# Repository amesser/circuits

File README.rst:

MPP Solar Battery Charger
=========================

This project is about creating a Maximum Power Point
Solar Battery Charger made of analog components only. I
also tried to use commonly available parts and
renounce using highly integrated and specialized ICs.

The charger uses a DC-DC Converter in Buck topology to
optimize the operating point of the solar panel. The optimal
operating voltage is manually adjustable. The charger will 
not dynamically adapt this voltage. (This would require
a microcontroller)

The circuit is made for 200W solar input power from 
36 cell panels and 12V Lead-Acid Battery. It can be 
easily adapted for other input and battery voltages.

More information can be found here: :doc:`documentation/index`

Licenses
--------

The following licensing conditions hold for this work:

Copyright (c) 2018 by Andreas Messer. This work is licensed under the 
Creative Commons Attribution-ShareAlike 3.0 Unported License. To view 
a copy of this license, visit http://creativecommons.org/licenses/by-sa/3.0/.

Author
------

Andreas Messer <andi@bastelmap.de>

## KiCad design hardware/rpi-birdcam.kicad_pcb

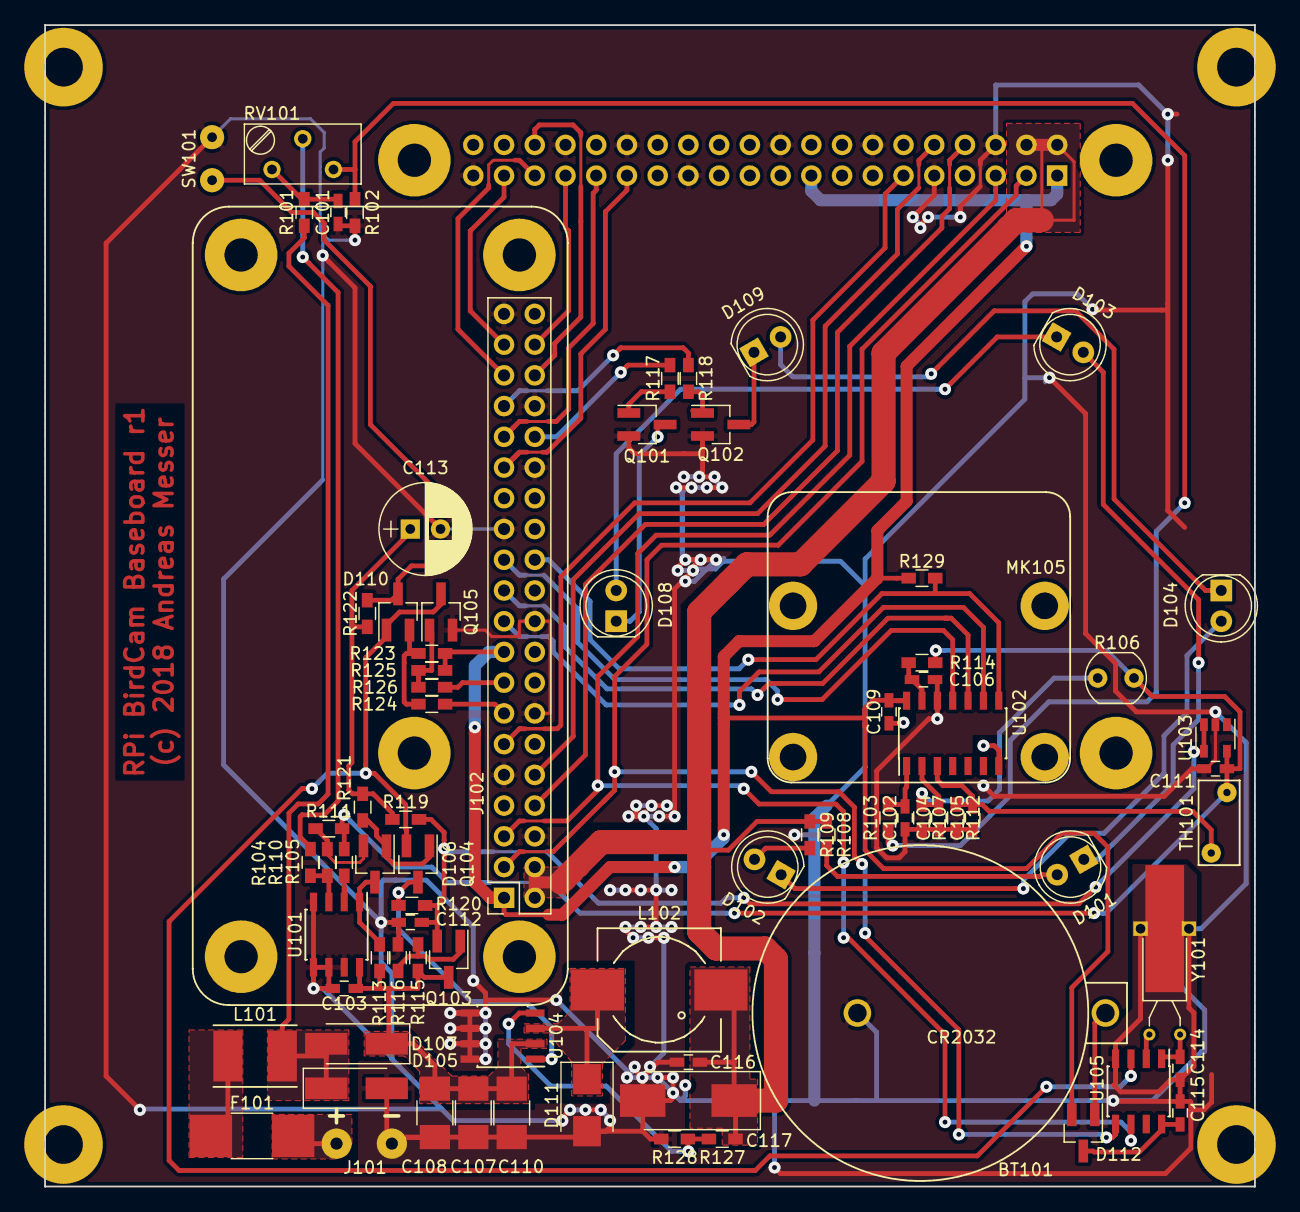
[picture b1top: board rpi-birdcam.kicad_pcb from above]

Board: 2 copper layers, 100.0 x 96.0 mm, 81 parts (1 on the bottom side), 63 nets.

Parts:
BT101: CR2032; keystone_electronics_106
C101, C102, C103, C104, C105, C106, C109, C111, C112, C116: 22nF; C_0603_HandSoldering
C107, C108, C110: 10µF; C_1210_HandSoldering
C113: 100µF; CP_Radial_D7.5mm_P2.50mm
C114: C; C_0603_HandSoldering
C115: 100nF; C_0603_HandSoldering
C117: 100µF; CP_Tantalum_Case-D_EIA-7343-31_Hand
D101, D102, D103, D104, D108, D109: LED; LED_D5.0mm
D105: D_TVS; D_SMA_Handsoldering
D106, D110, D112: BAT54C; SOT-23_Handsoldering
D107: SS14; D_SMA_Handsoldering
D111: SS22; D_SMB
F101: Polyfuse; R_1812_HandSoldering
J101: Conn_01x02; WireConnection_1.00mmDrill
J102: RPI; Raspberry_PI_Zero_V1.2_SocketStrip
J103: LTE Cat.1 Pi HAT; Raspberry_PI_ShieldConnector
L101: 47µH; Inductor_Taiyo-Yuden_NR-50xx_HandSoldering
L102: 22µH; Choke_SMD_Wuerth-WE-PDF_Handsoldering
MK103: Case; Kradex_Z59
MK105: Raspberry PI Camera Module V2.1; Raspberry_PI_Camera_Module_V2.1
Q101, Q102, Q103, Q104: BC847C; SOT-23_Handsoldering
Q105: Q_NPN_BEC; SOT-23_Handsoldering
R101: 22k; R_0603_HandSoldering
R102: 4.7k; R_0603_HandSoldering
R103, R104, R105, R107, R112: 100k; R_0603_HandSoldering
R106: LDR03; Resistor_LDR_5x4.1_RM3
R108, R109, R117, R118: R; R_0603_HandSoldering
R110, R113, R119: 470k; R_0603_HandSoldering
R111, R114, R122, R123, R125, R129: 10k; R_0603_HandSoldering
R115, R120: 47k; R_0603_HandSoldering
R116: 33k; R_0603_HandSoldering
R121: 2.2M; R_0603_HandSoldering
R124, R126: 1k; R_0603_HandSoldering
R127: 3.01k; R_0603_HandSoldering
R128: 976; R_0603_HandSoldering
RV101: 2k; Potentiometer_Trimmer_Bourns_3296Y
SW101: SW_Push; WireConnection_0.80mmDrill
TH101: PTC; RV_Disc_D7_W3.4_P5
U101: LM393; SOIC-8_3.9x4.9mm_Pitch1.27mm
U102: MCP3204; SOIC-14_3.9x8.7mm_Pitch1.27mm
U103: LM4120; SOT-23-5
U104: MIC4690; SOIC-8_3.9x4.9mm_Pitch1.27mm
U105: PCF8563; SOIC-8_3.9x4.9mm_Pitch1.27mm
Y101: 32.768 kHz; Crystal_AT310_d3.0mm_l10.0mm_Horizontal_1EP_style2

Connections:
/3.3V: C109.2, D112.2, J102.1, J102.17, J103.1, J103.17, R123.1, R125.1, R129.2, U102.14
/5V: C116.1, C117.1, J102.2, J102.4, J103.2, J103.4, L102.2, R108.1, R109.1, R127.2
/LTE_CTS: J102.36, J103.36
/LTE_DTR: J102.38, J103.33
/LTE_INH: J102.35, J103.35
/LTE_POWER: J102.29, J103.29
/LTE_RESET: J102.31, J103.31
/LTE_RST2: J102.37, J103.37
/LTE_RTS: J102.11, J103.11
/LTE_RXD: J102.10, J103.10
/LTE_TXD: J102.8, J103.8
/RPI_MISO: J102.21, U102.10
/RPI_MOSI: J102.19, U102.9
/RPI_SCL: J102.5, J103.5, U105.6
/RPI_SCLK: J102.23, U102.11
/RPI_SDA: J102.3, J103.3, U105.5
/VREF_2.5V: C111.1, R105.1, R106.1, R111.2, R114.2, TH101.1, U103.5
/~ADC_CE~: J102.24, R129.1, U102.8
/~PWR_BTN~: J102.13, R124.1
/~PWR_EN~: Q104.3, R120.2, U104.1
/~PWR_OFF~: J102.15, R126.1
/~PWR_ON~: D110.1, Q104.2, Q105.3, U105.3
/~UV~: D106.3, R113.2, U101.1
GND: BT101.2, C101.2, C102.1, C103.2, C104.1, C105.1, C106.2, C107.2, C108.2, C109.1, C110.2, C111.2, C112.2, C113.2, C114.2, C115.2, C116.2, C117.2, D105.2, D111.2, J101.2, J102.6, J102.9, J102.14, J102.20, J102.25, J102.30, J102.34, J102.39, J103.6, J103.9, J103.14, J103.20, J103.25, J103.30, J103.34, J103.39, Q101.2, Q102.2, Q105.2, R102.2, R107.2, R112.2, R116.2, R128.1, SW101.1, U101.4, U101.5, U101.6, U101.7, U102.7, U102.12, U103.2, U104.5, U104.6, U104.7, U104.8, U105.4, Y101.3
unnamed: BT101.1, D112.1
unnamed: C101.1, R101.2, RV101.1
unnamed: C102.2, R103.2, U102.1
unnamed: C103.1, C107.1, C108.1, C110.1, D107.1, Q103.3, R113.1, R115.1, U101.8, U104.2
unnamed: C104.2, R106.2, R107.1, U102.2
unnamed: C105.2, R112.1, TH101.2, U102.3
unnamed: C106.1, R114.1, U102.13
unnamed: C112.1, Q103.2, R119.2, R120.1, U103.3, U103.4
unnamed: C113.1, R119.1, R121.2, R122.2
unnamed: C114.1, U105.1, Y101.1
unnamed: C115.1, D112.3, U105.8
unnamed: D101.1, D103.2
unnamed: D101.2, R108.2
unnamed: D102.1, D104.2
unnamed: D102.2, R109.2
unnamed: D103.1, D108.2
unnamed: D104.1, D109.2
unnamed: D105.1, D107.2, L101.2, R101.1
unnamed: D106.1, Q104.1, R121.1
unnamed: D106.2, R110.1, R111.1
unnamed: D108.1, Q101.3
unnamed: D109.1, Q102.3
unnamed: D110.2, R123.2, R124.2
unnamed: D110.3, R122.1, SW101.2
unnamed: D111.1, L102.1, U104.3
unnamed: F101.1, L101.1
unnamed: F101.2, J101.1
unnamed: J102.32, R117.1
unnamed: J102.33, R118.1
unnamed: Q101.1, R117.2
unnamed: Q102.1, R118.2
unnamed: Q103.1, R115.2, R116.1
unnamed: Q105.1, R125.2, R126.2
unnamed: R102.1, R103.1, RV101.3
unnamed: R104.1, R110.2, U101.3
unnamed: R104.2, RV101.2
unnamed: R105.2, U101.2
unnamed: R127.1, R128.2, U104.4
unnamed: U105.2, Y101.2

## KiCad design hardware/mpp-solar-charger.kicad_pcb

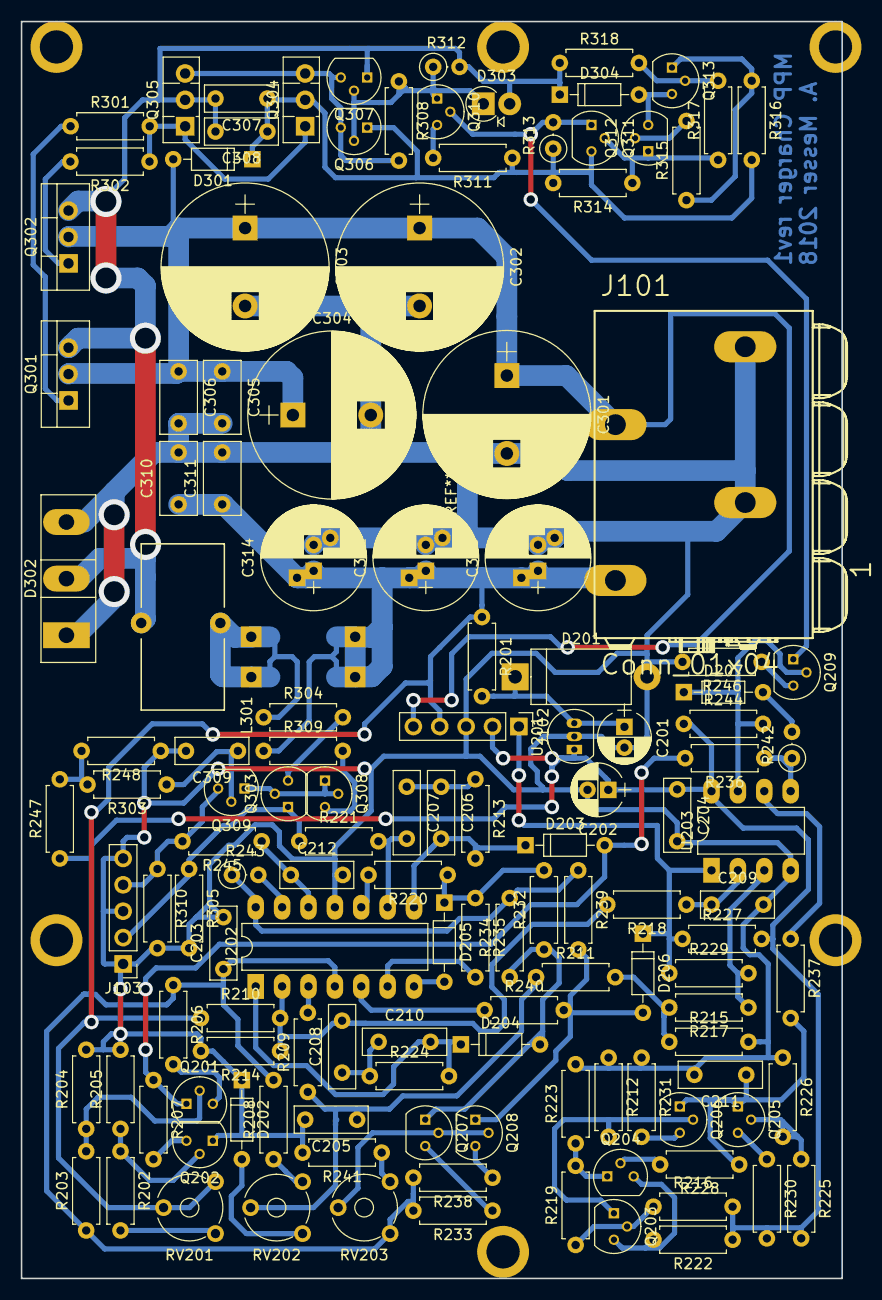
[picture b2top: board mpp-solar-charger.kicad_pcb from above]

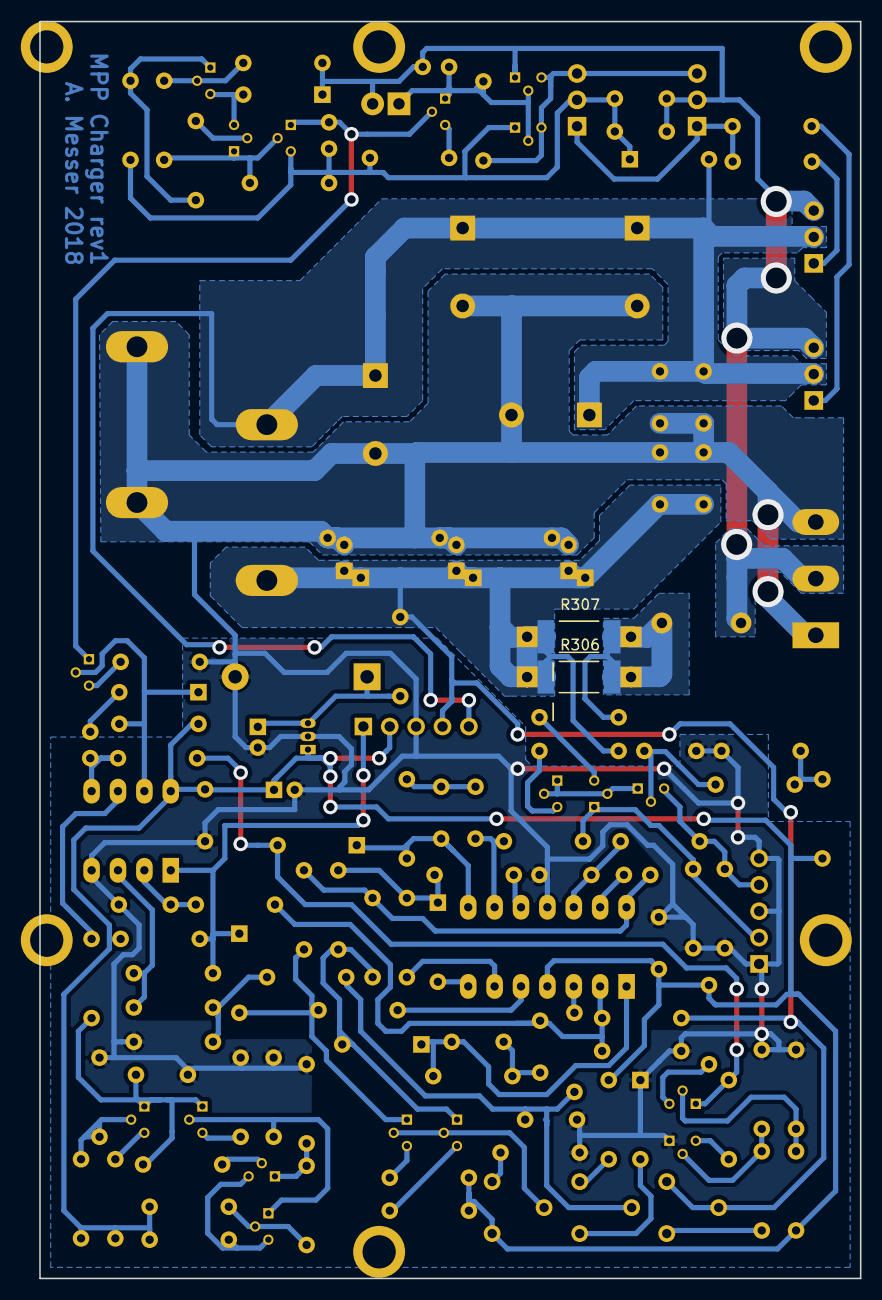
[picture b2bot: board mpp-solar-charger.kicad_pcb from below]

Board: 2 copper layers, 79.0 x 121.0 mm, 135 parts (2 on the bottom side), 75 nets.

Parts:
C201, C202: CP; CP_Radial_D5.0mm_P2.00mm
C203, C204, C205, C209, C212, C307, C308, C309: 100nF; C_Rect_L7.0mm_W2.5mm_P5.00mm
C206: 470pF; C_Disc_D8.0mm_W2.5mm_P5.00mm
C207: 4.7nF; C_Disc_D8.0mm_W2.5mm_P5.00mm
C208: 560pF; C_Disc_D8.0mm_W2.5mm_P5.00mm
C210: 100pF; C_Disc_D8.0mm_W2.5mm_P5.00mm
C211: 1nF; C_Disc_D8.0mm_W2.5mm_P5.00mm
C301, C302, C303, C304: CP; CP_Radial_D16.0mm_P7.50mm
C305, C306, C310, C311: 220nF; C_Rect_L7.0mm_W3.5mm_P5.00mm
C312, C313, C314: 1000µF/16V KZG; CP_Radial_D10.0mm_P2.50mm_P5.00mm
D201: D_TVS; D_DO-201_P12.70mm_Horizontal
D202, D203, D204, D205, D206, D207, D301, D304: D; D_DO-35_SOD27_P7.62mm_Horizontal
D302: MBR4045PT; TO-247_TO-3P_Vertical
D303: D_Zener; D_DO-41_SOD81_P2.54mm_Vertical_AnodeUp
J101: Conn_01x04; 2606-1104_020-000
J102, J103: Conn_01x05; Pin_Header_Straight_1x05_Pitch2.54mm
L301: L; Choke_Toroid_8x16mm_Vertical
Q201, Q202, Q203, Q204, Q205, Q207, Q208, Q303, Q307, Q308, Q310, Q311: Q_PNP_CBE; TO-92_Molded_Narrow
Q206, Q209, Q306, Q309, Q312, Q313: Q_NPN_CBE; TO-92_Molded_Narrow
Q301, Q302: IRFZ48N; TO-220-3_Vertical
Q304: BD135; TO-126_Vertical
Q305: BD136; TO-126_Vertical
R201: 100; R_Axial_DIN0207_L6.3mm_D2.5mm_P7.62mm_Horizontal
R202: 68k; R_Axial_DIN0207_L6.3mm_D2.5mm_P7.62mm_Horizontal
R203, R219: 22k; R_Axial_DIN0207_L6.3mm_D2.5mm_P7.62mm_Horizontal
R204: 33k; R_Axial_DIN0207_L6.3mm_D2.5mm_P7.62mm_Horizontal
R205, R206, R207, R212, R220, R221, R230: 4.7k; R_Axial_DIN0207_L6.3mm_D2.5mm_P7.62mm_Horizontal
R208, R209, R210, R213, R222, R223, R225, R227, R228, R232, R233, R235, R238, R239, R240, R244, R246, R305, R310, R314, R315: 10k; R_Axial_DIN0207_L6.3mm_D2.5mm_P7.62mm_Horizontal
R211: 5.6k; R_Axial_DIN0207_L6.3mm_D2.5mm_P7.62mm_Horizontal
R214: 1.3k; R_Axial_DIN0207_L6.3mm_D2.5mm_P7.62mm_Horizontal
R215: 220k; R_Axial_DIN0207_L6.3mm_D2.5mm_P7.62mm_Horizontal
R216, R217, R224, R226, R234, R248: 47k; R_Axial_DIN0207_L6.3mm_D2.5mm_P7.62mm_Horizontal
R218, R241, R245, R247, R316, R318: 100k; R_Axial_DIN0207_L6.3mm_D2.5mm_P7.62mm_Horizontal
R229: 1M; R_Axial_DIN0207_L6.3mm_D2.5mm_P7.62mm_Horizontal
R231, R303, R308, R311: 470; R_Axial_DIN0207_L6.3mm_D2.5mm_P7.62mm_Horizontal
R236, R237, R304, R309: 1k; R_Axial_DIN0207_L6.3mm_D2.5mm_P7.62mm_Horizontal
R242: 1M; R_Axial_DIN0207_L6.3mm_D2.5mm_P2.54mm_Vertical
R243: 100k; R_Axial_DIN0207_L6.3mm_D2.5mm_P2.54mm_Vertical
R301, R302: 1; R_Axial_DIN0207_L6.3mm_D2.5mm_P7.62mm_Horizontal
R306, R307: R; Resistor_SMD+THTuniversal_2512_RM10_HandSoldering
R312: 6.8k; R_Axial_DIN0207_L6.3mm_D2.5mm_P2.54mm_Vertical
R313: 2.2k; R_Axial_DIN0207_L6.3mm_D2.5mm_P2.54mm_Vertical
R317: 470k; R_Axial_DIN0207_L6.3mm_D2.5mm_P7.62mm_Horizontal
RV201, RV203: 20k; Potentiometer_Trimmer_Piher_PT-6v_Horizontal
RV202: 10k; Potentiometer_Trimmer_Piher_PT-6v_Horizontal
U201: LP2950L-5.0; TO-92_Inline_Narrow_Oval
U202: LM324; DIP-14_W7.62mm_LongPads
U203: LM393; DIP-8_W7.62mm_LongPads

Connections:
/Controller/+5V: C202.1, C203.1, C204.1, J102.2, R203.1, R206.1, R208.2, R216.2, R222.1, R225.2, R227.2, R230.2, R233.2, R238.2, R244.1, R247.1, RV203.3, U201.1, U202.4, U203.8
/Controller/CHARGED: D206.1, J102.1, R227.1, R229.1, U203.1
/Controller/UMIN: D206.2, Q208.1, R239.2, R240.2
/Controller/UREF: J103.4, Q309.3, R245.2, R310.1
/Controller/UREG: D204.2, Q207.1, R232.1, R234.1
/Controller/USAW: C211.1, Q205.1, Q206.1, R228.1, R237.2
/Controller/USENSE: J103.2, Q303.1, R221.1, R305.1
/Controller/USET: R247.2, R248.2, R303.2
/Controller/VBAT: C310.1, C311.1, C312.1, C313.1, C314.1, J101.1, J102.4, R201.1, R210.1, R306.1, R307.1, R309.1, RV201.1, RV201.2
/Controller/~SWITCH: Q209.1, Q310.2, Q311.1, R313.2
/Power-Stage/VSOLAR: C301.1, C302.1, C303.1, C304.1, C305.1, C306.1, D301.2, J101.3, J102.5, Q301.2, Q302.2
GND: C201.2, C202.2, C203.2, C204.2, C205.2, C209.2, C211.2, C212.2, C301.2, C302.2, C303.2, C304.2, C305.2, C306.2, C309.2, C310.2, C311.2, C312.2, C313.2, C314.2, D201.2, D202.1, D302.1, D302.3, J101.2, J101.4, J102.3, J103.1, J103.3, J103.5, Q202.1, R204.2, R205.2, R212.1, R214.2, R215.2, R223.2, R226.1, R231.1, R241.2, R246.2, R248.1, R305.2, R310.2, U201.2, U202.11, U203.4
unnamed: C201.1, D201.1, R201.2, U201.3
unnamed: C205.1, R209.1, R211.1, RV202.2
unnamed: C206.1, C207.1, R213.1
unnamed: C206.2, D203.1, R213.2, U202.8
unnamed: C207.2, R221.2, U202.9
unnamed: C208.1, C210.1, R224.1
unnamed: C208.2, R210.2, R214.1, R218.2, U202.2
unnamed: C209.1, R218.1, U203.2
unnamed: C210.2, D204.1, R224.2, U202.1
unnamed: C212.1, R245.1, U202.12
unnamed: C307.1, C308.1, D301.1, Q304.2, Q306.1, Q311.3, R311.1, R313.1, R314.2, R316.2
unnamed: C307.2, C308.2, D302.2, D303.2, D304.1, L301.1, Q301.3, Q302.3, Q305.2, Q307.1, R312.2, R318.1
unnamed: C309.1, Q309.2, R303.1
unnamed: D202.2, RV202.3
unnamed: D203.2, Q201.1, R207.1, R236.2
unnamed: D205.1, R220.1, R232.2, R235.1
unnamed: D205.2, U202.7
unnamed: D207.1, Q209.2, R244.2, U203.7
unnamed: D207.2, R242.2
unnamed: D303.1, Q306.2, Q307.2, Q310.1, R308.1, R312.1
unnamed: D304.2, Q312.3, Q313.3
unnamed: L301.2, R304.1, R306.2, R307.2
unnamed: Q201.2, R203.2, R204.1
unnamed: Q201.3, R206.2
unnamed: Q202.2, R202.1, R205.1
unnamed: Q202.3, R207.2
unnamed: Q203.1, Q206.2, R212.2
unnamed: Q203.2, R216.1, R219.1
unnamed: Q203.3, Q204.3, R222.2
unnamed: Q204.1, R219.2, R223.1
unnamed: Q204.2, R228.2
unnamed: Q205.2, R225.1, R226.2
unnamed: Q205.3, R230.1
unnamed: Q206.3, R231.2
unnamed: Q207.2, Q208.2, RV203.2
unnamed: Q207.3, R233.1
unnamed: Q208.3, R238.1
unnamed: Q209.3, R246.1
unnamed: Q301.1, R301.1
unnamed: Q302.1, R302.2
unnamed: Q303.2, Q308.1, Q308.2, Q309.1
unnamed: Q303.3, R304.2
unnamed: Q304.1, Q305.1, R301.2, R302.1
unnamed: Q304.3, Q305.3, Q306.3, Q307.3, R308.2
unnamed: Q308.3, R309.2
unnamed: Q310.3, R311.2
unnamed: Q311.2, Q312.1, R314.1, R317.1
unnamed: Q312.2, R315.2
unnamed: Q313.1, R315.1, R316.1
unnamed: Q313.2, R317.2, R318.2
unnamed: R202.2, RV201.3
unnamed: R208.1, RV202.1
unnamed: R209.2, U202.3
unnamed: R211.2, R215.1, R217.2
unnamed: R217.1, R229.2, U203.3
unnamed: R220.2, U202.10
unnamed: R234.2, R239.1, R243.1, U202.14
unnamed: R235.2, U202.6
unnamed: R236.1, R242.1, U203.5
unnamed: R237.1, U203.6
unnamed: R240.1, U202.5
unnamed: R241.1, RV203.1
unnamed: R243.2, U202.13

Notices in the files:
board/3in1-calibrator/3in1-calibrator.kicad_pcb:
(c) 2015 Andreas Messer
board/amplifier/radar-amplifier.kicad_pcb:
(c) 2016 Andreas Messer
hardware/mpp-solar-charger.kicad_pcb:
Copyright (c) 2018 Andreas Messer
